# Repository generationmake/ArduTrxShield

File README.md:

# ArduTrxShield
ArduTrx - Open Source Hamradio Transceiver for Arduino compatible to Arduino Uno

## PCB

### Top

### Bottom

## License

This hardware is licensed under the CERN OHL v. 1.2

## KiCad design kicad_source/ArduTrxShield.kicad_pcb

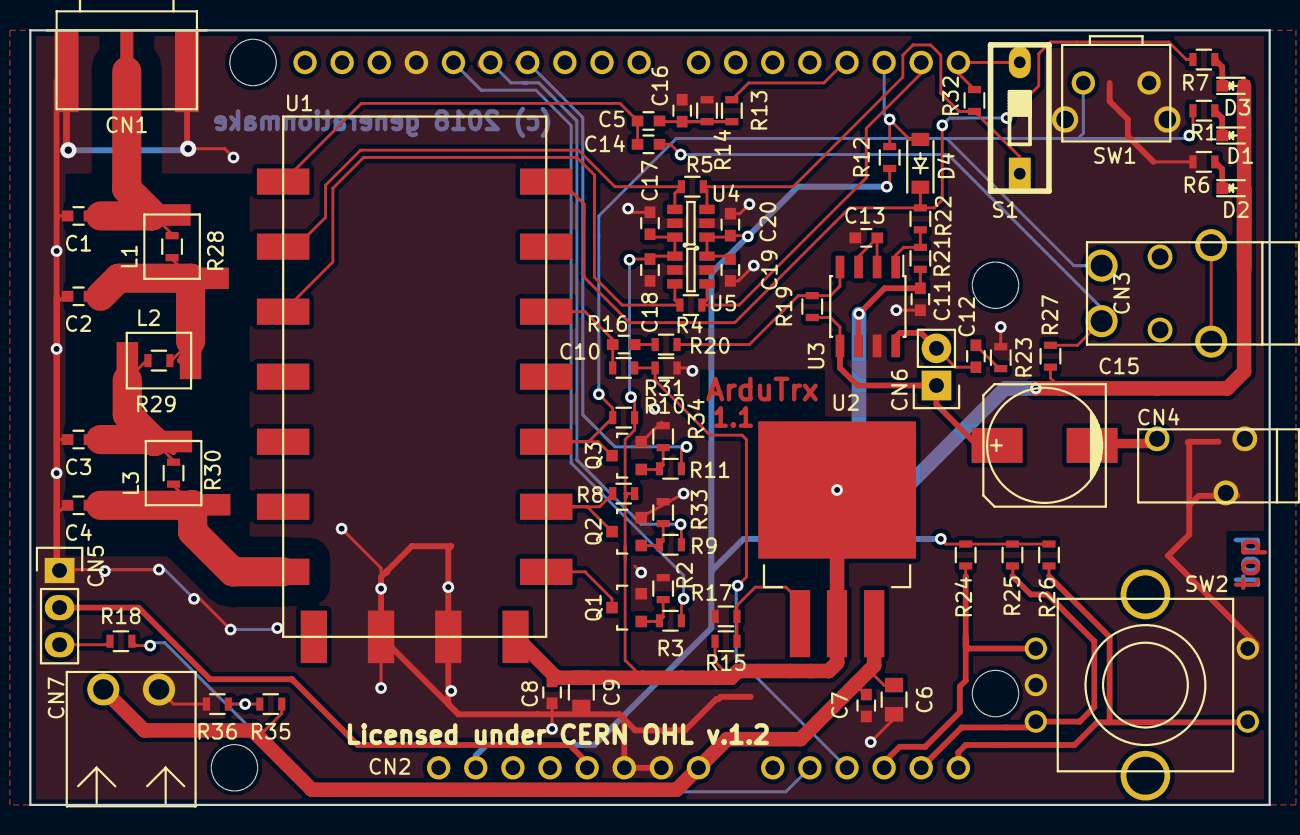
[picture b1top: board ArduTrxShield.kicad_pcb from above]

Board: 2 copper layers, 84.8 x 53.0 mm, 81 parts (0 on the bottom side), 48 nets.

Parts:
C1, C4: 30pF; C_0603
C2, C3: 47pF; C_0603
C5, C7, C8, C10, C11, C12, C14, C16, C17, C18, C19, C20: 100nF; C_0603
C6, C9: 10uF; C_0805
C13: 1uF; C_0603
C15: UWT1A471MNL1GS; c_elec_8x10.5
CN1: 60312202114509; WR-SMA-PCB
CN2: ARDUINO
CN3: LUM 1503-07; 1503_07
CN4: LUM 1501-03; 1501_03
CN5: 61300311121; Pin_Header_Straight_1x03
CN6: 61300211121; Pin_Header_Straight_1x02
CN7: 691322310002; WR-TBL_691322310002
D1: 150060RS75000; LED_0603
D2: 150060YS75000; LED_0603
D3: 150060GS75000; LED_0603
D4: BAT46ZFILM; SOD-123
L1, L2, L3: 744912156; WE-CAIR_4248
Q1, Q2, Q3: 2N7002; SOT-23
R1, R6, R7, R8, R10, R14, R16, R24, R25, R26, R31: 1k; R_0603
R2, R12, R13, R21, R27, R33, R34: 4k7; R_0603
R3, R9, R11, R18, R22: 100; R_0603
R4, R5, R28, R29, R30, R32: DNI; R_0603
R15: 121; R_0603
R17: 300; R_0603
R19, R20, R36: 20k; R_0603
R23: 2k; R_0603
R35: 100k; R_0603
S1: 418117270901; dip_1-300
SW1: 431256058736; WE_4312x6xxx7x6
SW2: 482009514001; ALPS_EC11E
U1: DRA818
U2: LM1085IS-ADJ; TO-263-3Lead
U3: LM4871; SOIC-8_3.9x4.9mm_Pitch1.27mm
U4, U5: SN74LVC1T45; SOT-23-6

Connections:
+5V: CN2.27, CN5.2
/AF_OUT: C10.2, R16.1, U1.3
/AF_OUT_R: CN2.21, R16.2, R31.1
/ANT0: C4.1, L3.2, R30.1, U1.12
/ANT1: C3.1, L2.2, L3.1, R29.1, R30.2
/ANT2: C2.1, L1.2, L2.1, R28.1, R29.2
/ANT3: C1.1, CN1.1, L1.1, R28.2
/ENC_A: CN2.20, R24.2, SW2.A
/ENC_B: CN2.19, R25.2, SW2.B
/ENC_SW: CN2.18, R26.2, SW2.E
/GPS_RX: CN2.22, R18.1, R35.2, R36.1
/H_L: Q1.3, U1.7
/H_L_Q: CN2.13, R3.1
/MIC: C14.1, CN3.2, R27.2
/MIC_IN: C5.2, C14.2, U1.18
/MIC_IN_R: CN2.3, R13.1
/PD: Q2.3, R8.2, U1.6
/PD_Q: CN2.12, R9.1
/PTT: CN3.1, Q3.3, R1.2, R10.2, SW1.3, U1.5
/PTT_Q: CN2.11, R11.1
/RXD: CN2.0, R32.1, S1.2
/RXD_R: R5.2, U1.17, U5.4
/RXD_S: R5.1, R32.2, S1.1, U5.3
/SPKR: C15.2, CN4.3
/SQ: D4.1, R7.2, R22.2, U1.1
/SQ_R: CN2.2, D4.2, R12.2
/TXD: CN2.1, R4.1, U4.4
/TXD_R: R4.2, U1.16, U4.3
GND: C1.2, C2.2, C3.2, C4.2, C6.2, C7.2, C8.2, C9.2, C11.2, C13.2, C16.2, C17.2, C18.2, C19.2, C20.2, CN1.2, CN1.3, CN1.4, CN1.5, CN2.14, CN2.25, CN2.26, CN4.1, CN4.2, CN5.1, CN7.2, Q1.2, Q2.2, Q3.2, R2.2, R6.2, R14.2, R17.2, R23.2, R31.2, R33.2, R34.2, R36.2, SW1.1, SW1.2, SW1.4, SW2.C, SW2.D, U1.9, U1.10, U3.7, U4.2, U4.5, U5.2, U5.5
unnamed: C10.1, R20.2
unnamed: C12.1, CN6.2, U3.8
unnamed: C12.2, R23.1
unnamed: C13.1, U3.2, U3.3
unnamed: C15.1, CN6.1, R19.1, U3.5
unnamed: C5.1, C16.1, R13.2, R14.1
unnamed: CN5.3, R18.2
unnamed: D1.1, R1.1
unnamed: D2.1, R6.1
unnamed: D3.1, R7.1
unnamed: Q1.1, R2.1, R3.2
unnamed: Q2.1, R9.2, R33.1
unnamed: Q3.1, R11.2, R34.1
unnamed: R15.2, R17.1, U2.1
unnamed: R19.2, R20.1, U3.4
unnamed: R21.2, R22.1, U3.1
VCC: C8.1, C9.1, C11.1, C17.1, C18.1, D1.2, D2.2, D3.2, R8.1, R10.1, R15.1, R21.1, R27.1, U1.8, U2.2, U2.4, U3.6, U4.1, U5.6
VIN: C6.1, C7.1, CN2.24, CN7.1, R35.1, U2.3
VIO: C19.1, C20.1, CN2.30, R12.1, R24.1, R25.1, R26.1, U4.6, U5.1

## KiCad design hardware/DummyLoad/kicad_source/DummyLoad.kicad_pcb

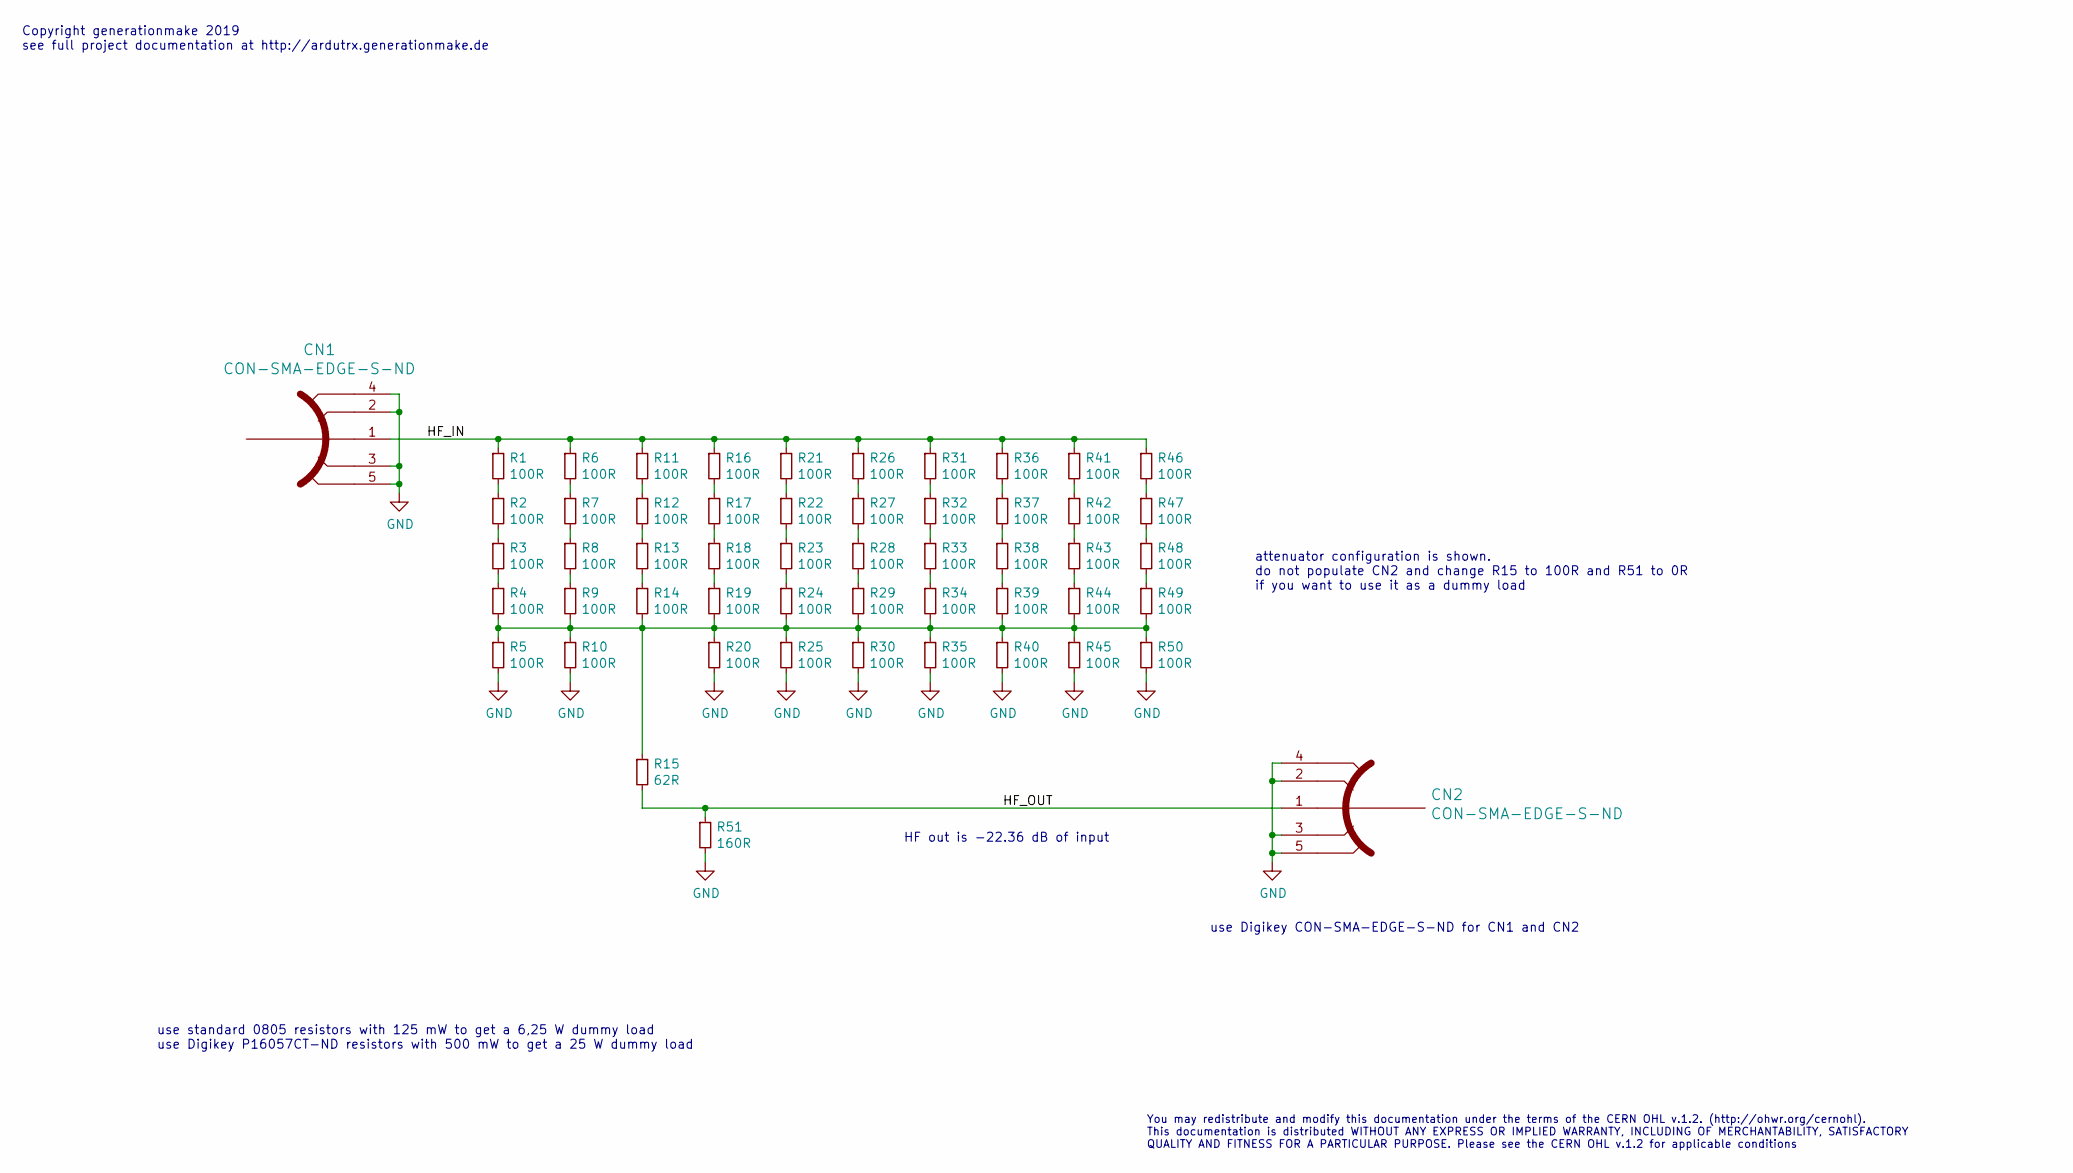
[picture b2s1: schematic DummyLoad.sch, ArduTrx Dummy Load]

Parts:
CN1, CN2: CON-SMA-EDGE-S-ND; WR-SMA-PCB
R1, R2, R3, R4, R5, R6, R7, R8, R9, R10, R11, R12, R13, R14, R16, R17, R18, R19, R20, R21, R22, R23, R24, R25, R26, R27, R28, R29, R30, R31, R32, R33, R34, R35, R36, R37, R38, R39, R40, R41, R42, R43, R44, R45, R46, R47, R48, R49, R50: 100R; R_0805
R15: 62R; R_0805
R51: 160R; R_0805

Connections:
/HF_IN: CN1.1, R1.1, R6.1, R11.1, R16.1, R21.1, R26.1, R31.1, R36.1, R41.1, R46.1
/HF_OUT: CN2.1, R15.2, R51.1
GND: CN1.2, CN1.3, CN1.4, CN1.5, CN2.2, CN2.3, CN2.4, CN2.5, R5.2, R10.2, R20.2, R25.2, R30.2, R35.2, R40.2, R45.2, R50.2, R51.2
unnamed: R1.2, R2.1
unnamed: R2.2, R3.1
unnamed: R3.2, R4.1
unnamed: R6.2, R7.1
unnamed: R7.2, R8.1
unnamed: R8.2, R9.1
unnamed: R4.2, R5.1, R9.2, R10.1, R14.2, R15.1, R19.2, R20.1, R24.2, R25.1, R29.2, R30.1, R34.2, R35.1, R39.2, R40.1, R44.2, R45.1, R49.2, R50.1
unnamed: R11.2, R12.1
unnamed: R12.2, R13.1
unnamed: R13.2, R14.1
unnamed: R16.2, R17.1
unnamed: R17.2, R18.1
unnamed: R18.2, R19.1
unnamed: R21.2, R22.1
unnamed: R22.2, R23.1
unnamed: R23.2, R24.1
unnamed: R26.2, R27.1
unnamed: R27.2, R28.1
unnamed: R28.2, R29.1
unnamed: R31.2, R32.1
unnamed: R32.2, R33.1
unnamed: R33.2, R34.1
unnamed: R36.2, R37.1
unnamed: R37.2, R38.1
unnamed: R38.2, R39.1
unnamed: R41.2, R42.1
unnamed: R42.2, R43.1
unnamed: R43.2, R44.1
unnamed: R46.2, R47.1
unnamed: R47.2, R48.1
unnamed: R48.2, R49.1

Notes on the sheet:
use Digikey CON-SMA-EDGE-S-ND for CN1 and CN2
HF out is -22.36 dB of input
use standard 0805 resistors with 125 mW to get a 6,25 W dummy load use Digikey P16057CT-ND resistors with 500 mW to get a 25 W dummy load
Copyright generationmake 2019 see full project documentation at http://ardutrx.generationmake.de
You may redistribute and modify this documentation under the terms of the CERN OHL v.1.2. (http://ohwr.org/cernohl). This documentation is distributed WITHOUT ANY EXPRESS OR IMPLIED WARRANTY, INCLUDING OF MERCHANTABILITY, SATISFACTORY QUALITY AND FITNESS FOR A PARTICULAR PURPOSE. Please see the CER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
attenuator configuration is shown. do not populate CN2 and change R15 to 100R and R51 to 0R if you want to use it as a dummy load

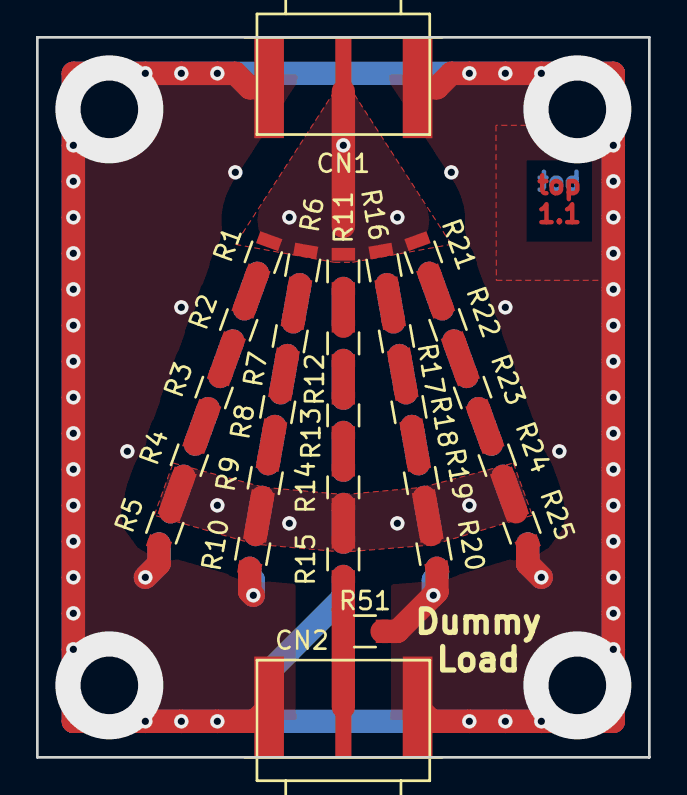
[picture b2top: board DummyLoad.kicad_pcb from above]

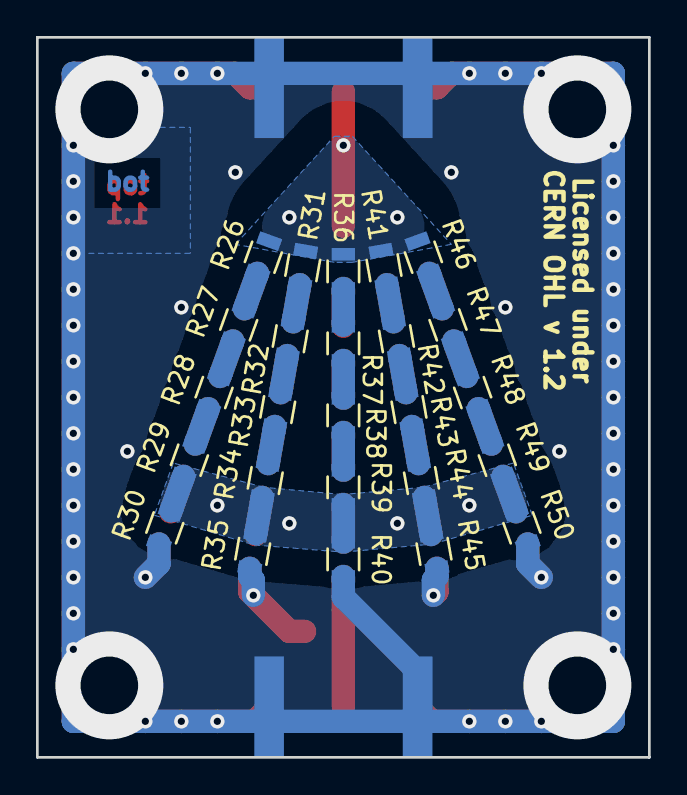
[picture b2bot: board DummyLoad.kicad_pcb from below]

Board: 2 copper layers, 34.0 x 40.0 mm, 53 parts (25 on the bottom side), 34 nets.

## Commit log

2018-07-16 initial release with ArduTrxShield CNC x1.0
2018-07-16 added CERN OHL licence
2018-07-16 added simple webpage for documentation
2018-07-16 update to version 1.1, changed C15 generated all data
2018-07-16 added zip file with all the data
2018-07-16 new folder for standard version
2018-07-17 updated layout and schematic
2018-07-18 generated gerber output
2018-07-20 renamed pdf files
2018-07-20 generated and updated output data and pdfs
2018-07-20 added zip files with data
2018-07-20 corrected BOM
2018-07-20 zip file with whole data
2018-08-19 updated docuemntation website
2018-08-21 updated schematic and layout of ArduTrxShield to version 1.1, see CHANGES.txt for details
2018-08-27 fixed schematic symbol links to library
2018-08-27 generated ArduTrxShield Version 1.1
2018-08-27 added DMR version. started with schematic and layout. needs to be checked
2018-09-19 updated footprints with 3D-models
2018-09-20 added 3d models
2018-09-23 updated some footprints with 3d models
2018-10-09 corrected schematic, updated layout
2018-11-20 updated description and generated renderings
2018-11-27 updated schematic and layout, connected some nets to 3.3v output of DMR818
2018-11-27 generated production files, pdf and gerber
2018-11-27 added zip file with production data
2018-11-28 updated documentation, added description of circuit and BOM
2018-12-02 added arduino pin usage
2019-03-08 updated documentation with description of software, added presentation from make munich
2019-03-17 updated BOM added farnell order numbers and links
2019-04-27 added step file
2019-04-27 added project DummyLoad
2019-04-27 added comments to schematic, added laber with license to pcb
2019-05-30 added documentation for dummyload
2019-05-30 moved files to the correct folder
2019-05-30 added pdf files, licence files, gerber files. updated data for release, generated zip file
2019-05-30 updated documentation, added link to aisler, added image
2019-07-22 corrected typo
2019-07-23 reworked schematic to have 50 ohms on input and output
2019-07-23 updated output files
2019-07-23 added zip file with data
2019-07-23 updated documentation
2020-11-29 removed unnecessary files
2020-11-29 moved files to correct folder
2020-11-29 updated to latest kicad version
2020-11-29 updated bom, added part numbers
2020-12-23 updated part numbers
2020-12-23 updated schematic pdf
2020-12-23 added images
2020-12-23 added readme

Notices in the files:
hardware/DummyLoad/kicad_source/DummyLoad.kicad_pcb:
This documentation describes Open Hardware and is licensed
under the CERN OHL v. 1.2.
hardware/DummyLoad/kicad_source/DummyLoad.sch:
This documentation describes Open Hardware and is licensed under the CERN OHL v. 1.2.
kicad_source/ArduTrxShield.kicad_pcb:
Licensed under CERN OHL v.1.2
(c) 2018 generationmake
